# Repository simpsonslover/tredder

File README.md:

# DIY hardware wallet

A personal-project hardware crypto wallet: RP2350 (Pico 2 W) + NXP SE050C2 secure element, with a colour screen, 4 buttons, microSD encrypted backups, BLE to a phone app, and a LiPo battery.

**Security is the priority. When convenience and security conflict, security wins, and the trade-off is written down.**

| Phase | Status | Where |
|---|---|---|
| 1. PCB (KiCad) | rev A routed, ERC/DRC clean, 19/19 circuit simulations pass, BOM | [hardware/](hardware/README.md) |
| 2. Firmware (Pico C SDK) | M1 wallet core done (8 347 host checks pass); M2 secure storage + PIN next | [firmware/](firmware/README.md) |
| 3. Mobile app (Expo dev build) | all screens built; 127 tests, lint/tsc/expo-doctor clean, Android bundle builds; talks to the mock device until firmware M5 adds the secure channel | [app/](app/README.md) |
| 4. Enclosure (tamper-evident) | not started | `enclosure/` |

Device ↔ app protocol: [protocol/PROTOCOL.md](protocol/PROTOCOL.md).

**Dev stack:** `tools/devstack/devstack.ps1` starts an Android emulator with the app, plus the [tredder device simulator](sim/README.md), and connects them ([how](tools/devstack/README.md)).

Every chain is built against testnets first (Bitcoin testnet, Sepolia, Solana devnet).

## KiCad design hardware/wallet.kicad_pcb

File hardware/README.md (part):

# Phase 1: main board (rev A)

KiCad project: `wallet.kicad_pro`. The schematic is saved in KiCad 8 format and opens in KiCad 8, 9, and 10. The PCB file was written by KiCad 10.0.7, which is installed on this machine, so **open it with KiCad 10**. KiCad 8 can't open boards saved by newer versions.

Everything is generated from **[tools/design.py](tools/design.py)**, which defines parts, pins, nets, and part numbers. The schematic, PCB netlist, and BOM come from that one file, so they can't drift apart.

| File | What it is |
|---|---|
| `wallet.kicad_sch` | Schematic (label-style, one A2 sheet, grouped by function) |
| `wallet.kicad_pcb` | 4-layer, 85.6 × 54 mm (credit card) PCB |
| `wallet.kicad_sym`, `wallet.pretty/` | Project symbols and two custom footprints |
| `bom/wallet_bom_full.csv` | Full BOM: MPN, LCSC, notes, and a **VERIFY** column |
| `bom/wallet_bom_jlc.csv` | JLCPCB assembly BOM (parts JLC can place) |
| `erc.rpt`, `drc.rpt` | Last ERC/DRC results |
| `tools/build.ps1` | Regenerates everything and reruns ERC/DRC |
| `sim/` | Circuit simulation of the whole board (ngspice), 18 tests: see §9 and [sim/README.md](sim/README.md) |
| `wallet.kicad_dru` + `wallet.kicad_pro` constraints | **JLCPCB's published multilayer limits** (jlcpcb.com/capabilities/pcb-capabilities, read 2026-11-01; re-check before ordering): track/space 0.09, via 0.15/0.25, PTH ring ≥ 0.15, PTH hole to track ≥ 0.28, SMD pad spacing ≥ 0.15, pad to track ≥ 0.1, copper to edge ≥ 0.2, NPTH ≥ 0.5, inner hole clearances 0.2/0.3, silkscreen text ≥ 1.0 mm / line ≥ 0.15 mm. KiCad's DRC uses them automatically |
| `jlcpcb-4L-real.edru` | The same JLCPCB limits as a **Fusion** design-rules file (load it in Fusion's DRC). It cannot hold the PTH-to-PTH 0.45 mm, PTH-hole-to-track 0.28 mm, NPTH and silkscreen limits; those are checked on the KiCad side. Also inside `mech/tredder-revA-fusion-ecad.zip` |
| `tools/gerber_drc.py` → `fab/gerber_drc.md` | **Independent DRC/DFM of the files the fab receives**, like EAGLE/Fusion's DRC and JLCPCB's DFM: renders the Gerbers at 10 µm (pygerber), reads the drill files and the IPC-D-356 netlist, and checks connectivity (opens = Fusion's air wires, shorts, inner planes included), clearance, width, annular rings, hole spacing, hole-to-copper, board edge, mask webs, silkscreen. Uses none of KiCad's checks. Proven on injected faults (missing plane, short, hairline). `export_fab.py` refuses to build the order if it reports an error. Needs `pip install pygerber numpy scipy pillow` |
| `tools/check_jlc.py` | JLCPCB hole-to-hole spacing (PTH ≥ 0.45 mm, other ≥ 0.2 mm), which KiCad 10's DRC does not check in this project; `export_fab.py` refuses to build the order without it |
| `tools/clean_tracks.py` | Removes Freerouting's duplicate segments and dead-end spurs (Fusion's "Wire Stub" check) without changing a connection; `route.py` runs it after every import |
| `tools/sync_values.py` | Pushes value-only changes from `design.py` into the routed PCB without touching copper |
| `breadboard/` | **Breadboard prototype** with the same Pico pins as the PCB: wiring picture, parts, wire-by-wire table, what it can and can't test (`tools/gen_breadboard.py`) |
| `mech/` | STEP for Fusion / MCAD: `tredder-revA.step` (detailed, for the enclosure) and `tredder-revA-sim.step` (clean solids for simulation). Setup: [mech/FUSION_SIM.md](mech/FUSION_SIM.md). Rebuild: `tools/export_mech.py` (KiCad python) |
| `mech/tredder-revA-fusion-ecad.zip` | The KiCad project for **Fusion's electronics import** (schematic + board). KiCad 10 writes nets in a form Fusion can't read (every pad comes in with no net), so `tools/export_fusion_ecad.py` writes the board with KiCad 9 net syntax and checks every net survives. Import `wallet.kicad_pro` from this zip, not from this folder |
| `3d/` | The project's own STEP models (display module, LiPo, and parts missing from KiCad's library), from `tools/gen_step_models.py` |

---

## 1. Block diagram

```
 USB-C ──F1──U1(ESD)──R3/R4(0Ω, DNP=charge-only)──► Pico TP2/TP3 (USB D-/D+)
   │ VBUS
   ├────────► Pico VBUS ──(Schottky on module)──► VSYS ◄──Q1 (load-share PFET)◄── SW1-A ◄── BT1 LiPo (J2)
   └──► U3 MCP73831 charger ───────────────────────────────────────────────────────┘ VBAT
                                                    SW1-B: 3V3_EN → GND (hard off, even on USB)

 Pico 2 W (RP2350 + CYW43439 BLE)
   I2C0  GP8/GP9  ──────► U2 NXP SE050C2         (VCC switched by Q2 = its reset; pull-ups on the SE supply)
   SPI0  GP0-3    ──────► J3 microSD            (VDD switched by Q3, soft-start, DET on GP6)
   SPI1  GP26/27  ──────► J4 2.0" ST7789 module (CS GP21, DC GP22, RST GP20, BL via Q4 on GP19,
                          module VCC switched by Q5 on GP18: unpowered in sleep)
   GP12-15        ──────► Back / Confirm / Up / Down (10k pull-ups + RC debounce)
   GP28 (ADC2)    ◄────── VBAT divider (after power switch, no drain when off)
   GP5            ◄────── charger STAT (5V→3.3V divider)
   SWD pads D1-D3 ──────► reachable from the back through the plated holes under the Pico (no debug connector)
```

## 2. Pin map

| GPIO | Function | | GPIO | Function |
|---|---|---|---|---|
| GP0 | SD MISO (SPI0 RX) | | GP14 | BTN UP |
| GP1 | SD CS (SPI0 CSn) | | GP15 | BTN DOWN |
| GP2 | SD SCK | | GP16 | unused |
| GP3 | SD MOSI | | GP17 | unused |
| GP4 | unused | | GP18 | LCD power enable (active low, Q5) |
| GP5 | CHG_STAT | | GP19 | LCD backlight (active low) |
| GP6 | SD card detect | | GP20 | LCD RST |
| GP7 | SD power enable (active low) | | GP21 | LCD CS |
| GP8 | SE SDA (I2C0) | | GP22 | LCD DC |
| GP9 | SE SCL (I2C0) | | GP26 | LCD SCK (SPI1) |
| GP10 | unused | | GP27 | LCD MOSI (SPI1) |
| GP11 | SE power enable (active low) | | GP28 | VBAT sense (ADC2) |
| GP12 | BTN BACK | | GP23-25, 29 | used inside the module by the radio |
| GP13 | BTN CONFIRM | | | |

All five switch controls (Q2 SE, Q3 SD, Q4 backlight, Q5 display power, and SW1) default to **off** when the MCU is in reset or unprogrammed.

## 3. Secure element: NXP SE050C2 (chosen over the SE050A2)

**U2 = NXP SE050C2, `SE050C2HQ1/Z01SDZ`** (HX2QFN20 / SOT1969-1: 3 × 3 × 0.32 mm, 0.4 mm pitch, centre pad to GND). **You buy it from an NXP-authorised distributor (Mouser / Digi-Key / Farnell) and solder it yourself.** It's left out of the JLCPCB BOM and placement file. LCSC lists it as C2659345, but with almost no stock.

**Why C2 rather than A2.** Both are the same chip, pinout and package, with the same certification (CC EAL6+), bus encryption (SCP03) and 50 kB of secure storage. The suffix is the configuration NXP loads at the factory:

| | **SE050C2** | SE050A2 |
|---|---|---|
| Public-key crypto | Full set: ECC (NIST, Brainpool, Ed25519/X25519, **Koblitz incl. secp256k1**) and RSA up to 4096 bit | A subset: ECC only, no RSA (NXP: the A/B variants "come with a subset of keys") |
| secp256k1, the Bitcoin/Ethereum curve | Users report ECDSA secp256k1 signing works on the C2 dev kit | Not confirmed for A |
| Dev kit for the breadboard | OM-SE050ARD is the C2 configuration | — |

The C2 gives up nothing against the A2, and keeps the option of doing secp256k1 operations inside the SE (for example a device attestation key the app can verify).

**What changed from the OPTIGA Trust M, and what that trades off:**

- **Bus protection.** The OPTIGA's Shielded Connection is replaced by the SE050's **Platform SCP03** (AES-encrypted and MACed APDUs). **Trade-off:** NXP publishes the default SCP03 keys for its dev kits, so the link is effectively plaintext until provisioning rotates them to device-unique keys stored in RP2350 OTP. Firmware must refuse to store any secret before that rotation.
- **PIN-gated secret.** On the SE050 this is an AES authentication object with MaxAttempts = 10 guarding a binary object (firmware `app/se.h`). **Trade-off:** Trezor's open-source PIN code was written for the OPTIGA. For the SE050 the references are NXP's AN12413 (APDU spec) and AN12514 (security guidelines), and Nitrokey 3, an open-source security key built on the SE050. The "attempt counted before the result" property must be re-verified on this chip in M2.
- **Soldering.** **Trade-off:** the pitch is 0.4 mm instead of 0.5 mm, which is harder by hand. Use flux, a fine tip or solder paste, and hot air or a hot plate, then check every side under a magnifier for bridges.
- **No reset pin.** The SE050 is reset by switching its supply off with Q2 for ≥ 40 ms (GP10 is now unused). ENA is tied high (deep power-down not used), VIN = VCC, VOUT open, and the unused contactless (LA/LB) and ISO7816 RST inputs go to GND, all per datasheet Table 5.
- **I2C pull-ups** R13/R14 now go to the switched SE supply, not +3V3, so an unpowered SE is never fed through its I/O pins.
- **Lifecycle.** Distributors list the SE050C2 as NRND (not recommended for new designs), with NXP steering new designs to newer SE05x parts. It is still stocked; **buy 2–3 spares now.**

**Phase 2 key scheme (design target):**
`seed_key = KDF(PIN-stretched secret, SE-held secret released after PIN check, RP2350 OTP secret)`.
An attacker needs the PIN, **and** must defeat the SE counter, **and** must read the MCU's OTP. Stealing one chip isn't enough.

## 4. Security decisions in this board (and what each trades away)

| Decision | Security gain | Convenience lost |
|---|---|---|
| R3/R4 0 Ω links on USB D+/D- (DNP in production) | Charge-only USB removes the whole USB stack and BOOTSEL/PICOBOOT as attack surface | Firmware updates then come via a signed image on microSD instead of USB |
| SW1 pole B grounds `3V3_EN` | Hard off, even when USB is plugged in; nothing runs while it's "off" | Can't wake from USB; must flip the switch |
| SE power switched (Q2), default off | Lets firmware hard-reset the SE and keep it unpowered when locked | One more GPIO and some firmware sequencing |
| Display module power-gated (Q5), and sleep locks the wallet | Sleep current 14 mA → 2.6 mA (≈ 8 days on BT1 instead of 1.5). Waking always needs the PIN, so a device left asleep is locked | Waking takes a button press + PIN; the display re-initialises (~0.3 s) |
| SD on its own SPI bus, power-gated (Q3) | Untrusted removable media can't share a bus with the display, and is unpowered unless in a backup flow | Need to power-cycle the card in firmware |
| No test points on SE I2C | Makes passive probing slightly harder (Platform SCP03 is the real defence) | Harder to debug the SE link (use a scope on the IC pins) |
| No debug connector or test pads (removed to keep the board simple) | Less to cover in production; SWD disabled in OTP anyway | Debugging means soldering wires to the Pico's underside SWD pads through the holes; voltages are probed on the parts themselves |
| External pull-ups on buttons | Immune to RP2350 erratum E9 (input pull-down latch) whatever the chip stepping | 8 passives |
| All parts on top, display module above them | Single-sided assembly is cheaper | Display must be removed to reach the Pico (BOOTSEL, SWD) |

## 5. Honest physical-security assessment

**What this design resists**
- **Lost or stolen device, casual or opportunistic attacker:** strong. Without the PIN, the seed is ciphertext in external flash. The SE wipes its secret after 10 tries, and that counter lives in the SE, not in the MCU.
- **Reading the flash chip** (desoldering the W25Q on the Pico module): gets ciphertext only. This is exactly why the seed must never be in flash in plain form.
- **Firmware replacement:** secure boot rejects unsigned images, and anti-rollback rejects old ones.
- **SWD debugging:** disabled permanently in OTP.
- **Sniffing the MCU↔SE bus:** defeated by Platform SCP03, once provisioning has replaced NXP's published default keys.

**What it does not fully resist (be aware)**
- **Fault injection on the RP2350 (voltage/EM/laser glitching).** In Raspberry Pi's 2024–25 RP2350 hacking challenge, researchers broke the A2 stepping with glitching, and one team extracted OTP secrets. The A4 stepping fixed several of these, and the glitch detectors help, but a well-equipped lab attacker with your device for days is **not** stopped by the RP2350 alone. That's why the SE secret is part of the key derivation: glitching the MCU alone then shouldn't be enough.
- **The SE itself:** EAL6+ resists most lab attacks within its certified scope, but no chip is unbreakable. A nation-state lab attack is out of scope.
- **Evil maid / supply-chain implant:** an attacker who opens the case, adds a keylogger on the buttons or a tap on the display SPI, and returns the device could capture the PIN or the seed shown during setup. Mitigations: the tamper-evident case (Phase 4), checking the seal every time, and a firmware attestation check against the SE (Phase 2). The board itself can't detect this when it's off; there's no battery-backed tamper mesh.
- **Wireless:** the CYW43439 runs a closed-source Infineon firmware blob loaded by the RP2350. A remote bug there is a real (if unlikely) risk. The BLE design treats the phone and the radio as untrusted (everything authenticated, confirm on device), but an air-gapped design such as SeedSigner or Coldcard with QR/SD is strictly safer. **This is the single biggest trade-off of putting Bluetooth in the device.**
- **Cold-boot / RAM remanence while unlocked:** the firmware wipes secrets after use, but an attacker who glitches a running, unlocked device has more options than one who gets a locked device.
- **$5 wrench attack:** use the BIP39 passphrase (hidden wallet) feature in Phase 2.

## 6. Check these before ordering ⚠

1. **SE050 footprint:** `NXP_HX2QFN-20-1EP_3x3mm_P0.4mm_EP1.7x1.7mm` is KiCad's WQFN-20 3×3 P0.4 land pattern (0.2 × 0.825 mm pads, 1.7 × 1.7 mm centre pad). It matches the EasyEDA footprint LCSC publishes for C2659345, and the pinout is datasheet rev 3.7 Figure 4 / Table 5. NXP's site blocks automated downloads, so I couldn't read the SOT1969-1 package drawing itself. **Compare the pads with NXP's SOT1969-1 "reflow soldering footprint" before ordering.**
2. **Display module pinout and outline:** J4 assumes the common 2.0" 240×320 ST7789V module order **GND, VCC, SCL, SDA, RES, DC, CS, BLK** and a ~60 × 36 mm outline (F.Fab rectangle). Waveshare and others use different orders. Buy the module first, then edit `NETS` in `design.py` to match. The firmware drives the panel landscape (`MADCTL 0x60` in `firmware/app/src/gfx.c`), assuming the module's native top edge points away from J4. If the picture is upside down on your module, use `0xA0`.
3. **LiPo connector polarity:** pin 1 = BAT+. Many cheap packs are wired reversed for JST-PH. A reversed pack destroys the charger. Use a cell **with a protection circuit (PCM)**, ≤ 50 × 34 × 6 mm to sit behind the board, ≥ 500 mAh (charge current is set to 500 mA by R5 = 2 kΩ). The design uses **BT1 = 1S LiPo "503035" (5.0 × 30 × 35 mm, 500 mAh, PCM, JST-PH 2.0 lead)**: not a board part: it is drawn as an outline on B.Fab, and its STEP model rides on J2, the connector it plugs into (`tools/add_battery.py`). This keeps every board part matched to a schematic symbol, which Fusion's import requires, stuck behind the left half with 0.5 mm foam tape, clear of the J4 header pins and the antenna. It is not in the JLC BOM: buy it separately and **check the lead polarity before plugging in**.
4. **LCSC numbers:** all checked against their LCSC product pages on 2026-11-02 (MPN, maker, value and package match for C1779, C19666, C22809, C4190, C23179, C424093). Stock was not visible there: JLCPCB's BOM step shows it for every line. Check it before paying.
5. **Pico 2 W underside pads:** USB D+/D- (TP2/TP3) and SWD (D1–D3) are **under** the module. The custom footprint adds 0.8 mm plated holes there so you can feed solder from the back. Otherwise reflow the module (stencil and hot plate). Test continuity before powering.
6. **Pico 2 W stepping:** confirm the RP2350 is stepping **A4** or later (the chip marking or `chip_id` in the bootrom). A4 includes the security fixes from the hacking challenge.
7. **Don't plug in both USB ports.** The Pico's own micro-USB is still on the module, under the display. Its VBUS ties to the same net. The case should block it.
8. **Antenna area:** keep metal (battery, screws, display frame) away from the right-hand 10 mm of the board. The battery must sit behind the left part of the board only (Phase 4).
9. **DPDT switch pinout:** this assumes the C&K JS202011JCQN pins 2 and 5 are the commons. Confirm with the datasheet.
10. **microSD card-detect:** this assumes the DM3AT DET switch closes to DET_A (tied to GND) when a card is inserted. Confirm with the datasheet; firmware can invert it if not.
11. **Routing:** see section 7. Review every autorouted trace yourself; don't send an autorouted security device to fab unseen.

## 7. Layout status

- Placement, board outline, 4-layer stack, and GND/3V3 pours are done.
  - In1 is solid GND.
  - In2 is a +3V3 plane.
  - The outer layers are GND fills.
- The Pico antenna keepout is respected.
- **Routing: complete draft.** GND/+3V3 pads get generated stub+via fanout to the planes (`gen_pcb.py: fanout`). The remaining signals were autorouted with Freerouting 2.1 (`tools/route.py`) on F.Cu/B.Cu only.
- **DRC: 0 unconnected, 0 clearance/short errors, 0 schematic-parity issues. ERC: 0 errors, 0 warnings.**
- What's left in `drc.rpt`:
  - 2 × "items not allowed": paste openings inside the stock Pico footprint's own RF keepout. These are harmless and come from the library footprint.
  - 2 × "starved thermal": USB-C shell tabs have one thermal spoke on F.Cu. They're still connected through the other layers.
  - Silkscreen overlap warnings: cosmetic, and JLC clips silk off pads.
- ⚠ **`tools/build.ps1 -Fresh` regenerates placement and DISCARDS routing.** After the first route, make changes in KiCad (F8 = update from schematic) or re-run `route.py`.

**Recommended manual clean-up in KiCad (before ordering):**
1. Fatten the VBUS, VBAT, and VSYS paths (≥ 0.5 mm) and keep them short.
2. Route USB D+/D- as a pair (USB 1.1 full-speed is forgiving, but keep it tidy).
3. Make sure no trace runs under the antenna keepout.
4. Stitch GND vias around the board edge and the Pico.
5. Run DRC with zero errors, then generate Gerbers using JLC's KiCad guide.

## 8. Bring-up / test plan (do this before Phase 2)

Test in this order and stop at the first failure.

1. **Bare board:** check continuity GND↔+3V3, GND↔VBUS, and GND↔VBAT. None should be shorted.
2. **Power, without the Pico:** connect USB-C through a USB power meter. Check:
   - VBUS is ~5 V.
   - The charger LED is off with no battery.
   - Adding the battery makes the LED light, and VBAT climbs to 4.2 V then the LED goes off.
3. **Fit the Pico.** Check:
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
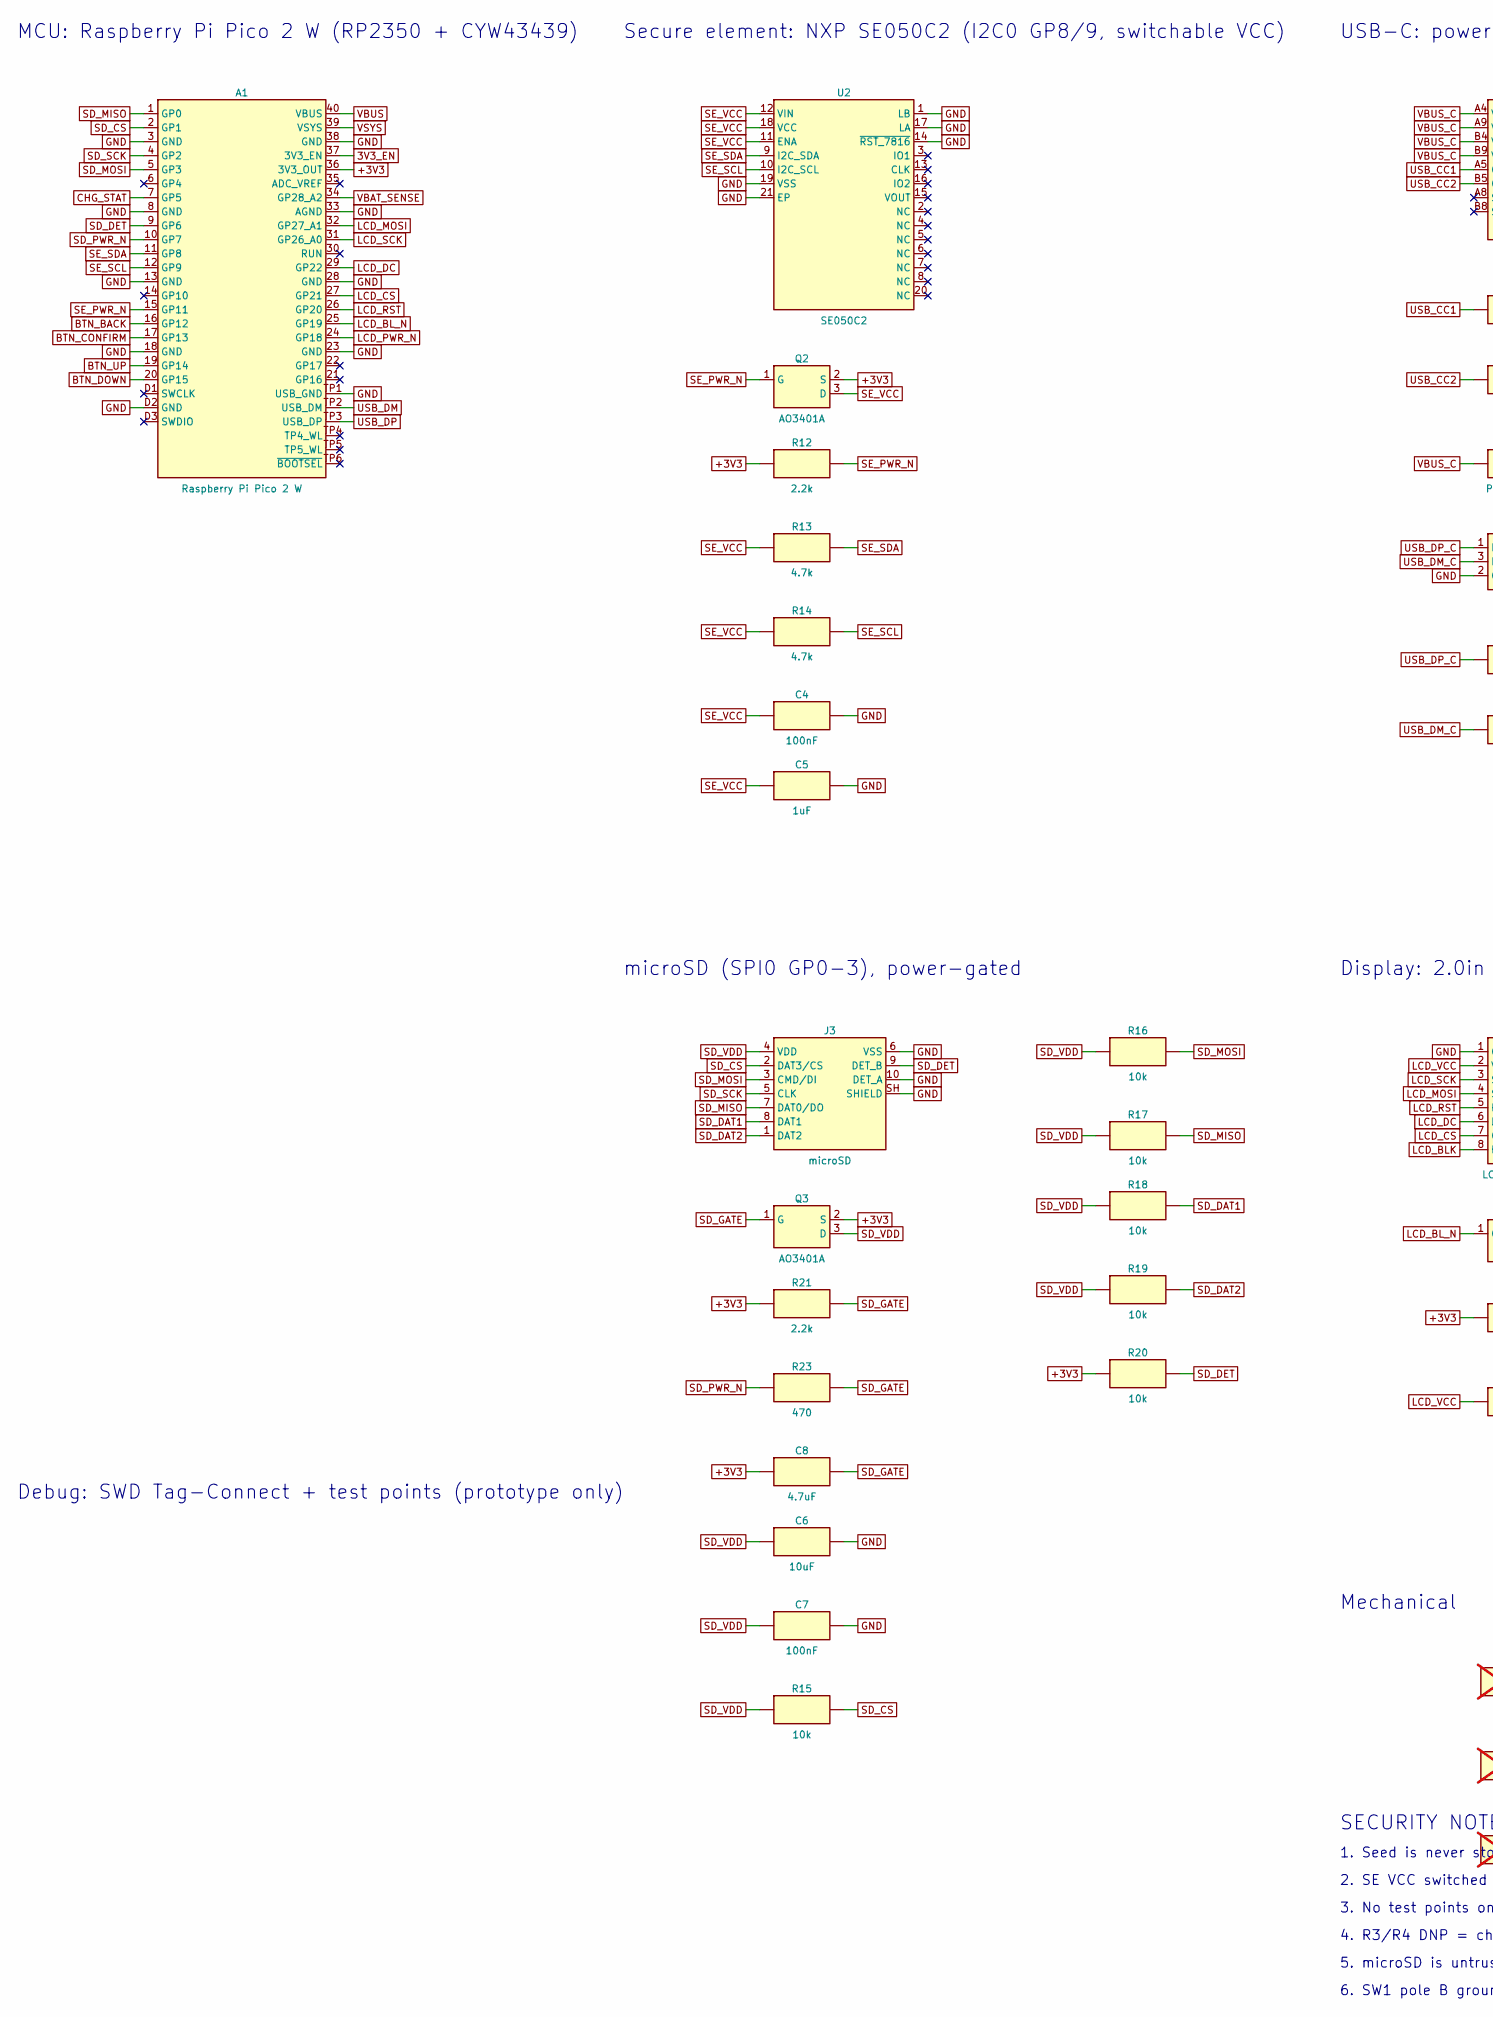
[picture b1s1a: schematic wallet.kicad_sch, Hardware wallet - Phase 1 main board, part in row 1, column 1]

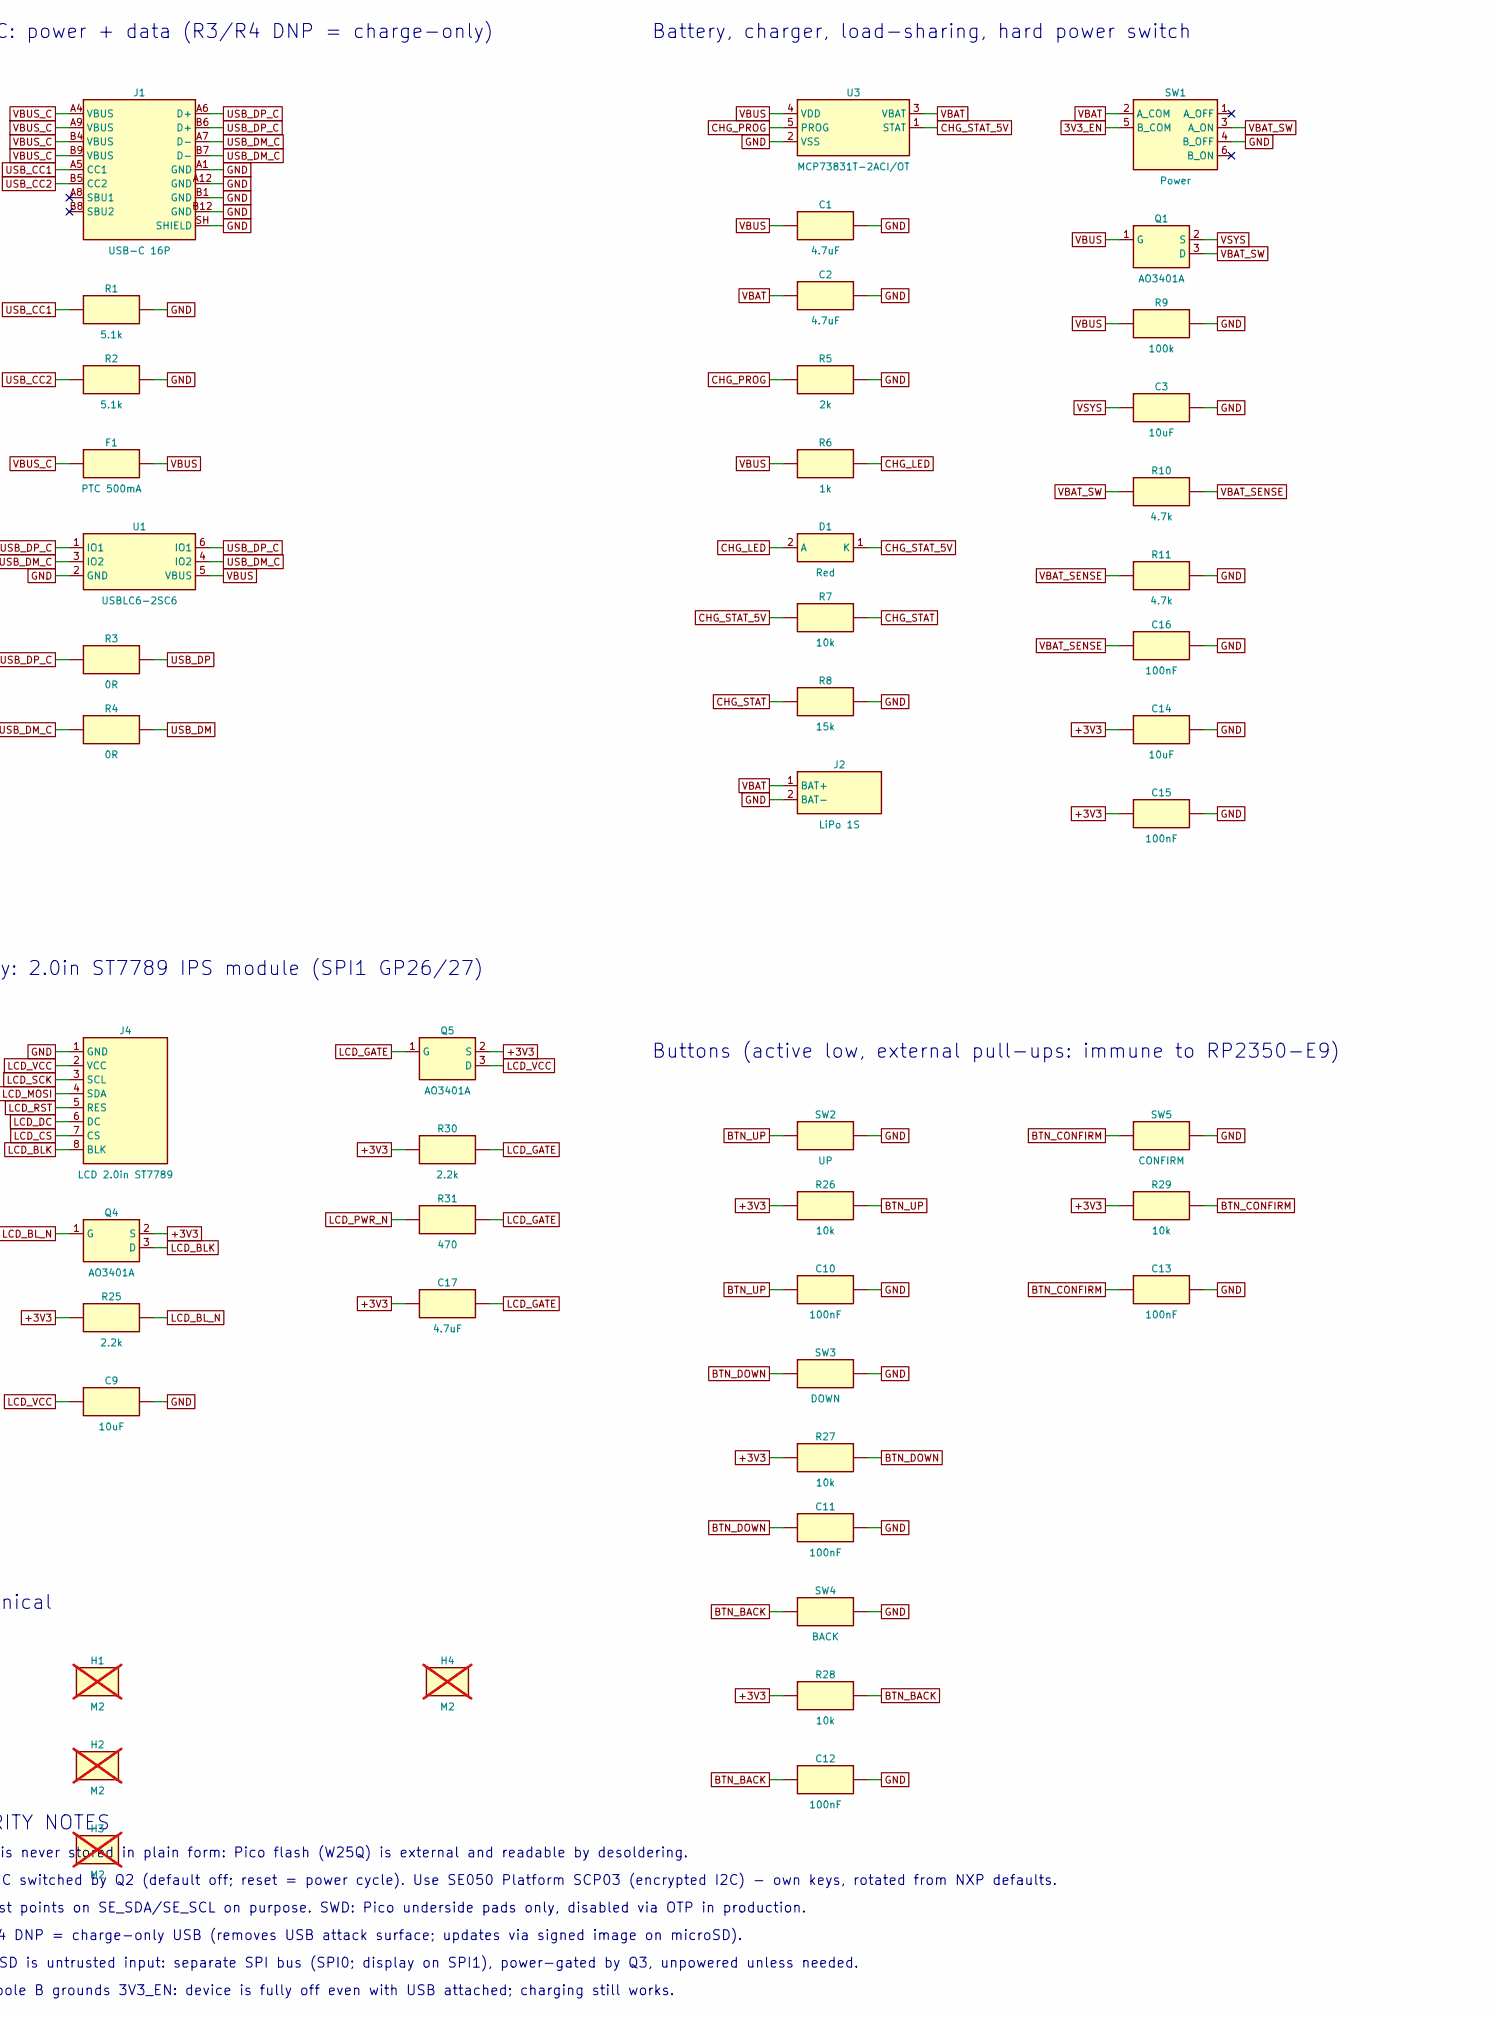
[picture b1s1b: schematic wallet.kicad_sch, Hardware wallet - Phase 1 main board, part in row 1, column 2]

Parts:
A1: Raspberry Pi Pico 2 W; RaspberryPi_Pico_2_W_SMD_SolderHoles; MPN SC1634 (Pico 2 W); LCSC C42394205
C1, C2: 4.7uF; C_0805_2012Metric; MPN CL21A475KAQNNNE; LCSC C1779
C3, C6, C9, C14: 10uF; C_0805_2012Metric; MPN CL21A106KAYNNNE; LCSC C15850
C4, C7, C10, C11, C12, C13, C15, C16: 100nF; C_0603_1608Metric; MPN CC0603KRX7R9BB104; LCSC C14663
C5: 1uF; C_0603_1608Metric; MPN CL10A105KB8NNNC; LCSC C15849
C8, C17: 4.7uF; C_0603_1608Metric; MPN CL10A475KO8NNNC; LCSC C19666
D1: Red; LED_0603_1608Metric; MPN KT-0603R; LCSC C2286
F1: PTC 500mA; Fuse_1206_3216Metric; MPN SMD1206-050 (JKSEMI, 6 V, 0.5 A hold, 1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; LCSC C2846128
H1, H2, H3, H4: M2; MountingHole_2.2mm_M2; MPN No part; not fitted
J1: USB-C 16P; USB_C_Receptacle_HRO_TYPE-C-31-M-12; MPN TYPE-C-31-M-12; LCSC C165948
J2: LiPo 1S; JST_PH_S2B-PH-SM4-TB_1x02-1MP_P2.00mm_Horizontal; MPN S2B-PH-SM4-TB(LF)(SN); LCSC C295747
J3: microSD; microSD_HC_Hirose_DM3AT-SF-PEJM5; MPN DM3AT-SF-PEJM5; LCSC C114218
J4: LCD 2.0in ST7789; PinSocket_1x08_P2.54mm_Vertical; MPN 2.54-1*8P female header, 8.5 mm (BOOMEL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; LCSC C27438
Q1, Q2, Q3, Q4, Q5: AO3401A; SOT-23; MPN AO3401A; LCSC C15127
R1, R2: 5.1k; R_0603_1608Metric; MPN 0603WAF5101T5E; LCSC C23186
R3, R4: 0R; R_0603_1608Metric; MPN 0603WAF0000T5E; LCSC C21189
R5: 2k; R_0603_1608Metric; MPN 0603WAF2001T5E; LCSC C22975
R6: 1k; R_0603_1608Metric; MPN 0603WAF1001T5E; LCSC C21190
R7, R15, R16, R17, R18, R19, R20, R26, R27, R28, R29: 10k; R_0603_1608Metric; MPN 0603WAF1002T5E; LCSC C25804
R8: 15k; R_0603_1608Metric; MPN 0603WAF1502T5E; LCSC C22809
R9: 100k; R_0603_1608Metric; MPN 0603WAF1003T5E; LCSC C25803
R10, R11, R13, R14: 4.7k; R_0603_1608Metric; MPN 0603WAF4701T5E; LCSC C23162
R12, R21, R25, R30: 2.2k; R_0603_1608Metric; MPN 0603WAF2201T5E; LCSC C4190
R23, R31: 470; R_0603_1608Metric; MPN 0603WAF4700T5E; LCSC C23179
SW1: Power; SW_DPDT_CK_JS202011JCQN; MPN JS202011JCQN; LCSC C221665
SW2: UP; SW_Push_1P1T_XKB_TS-1187A; MPN TS-1187A-B-A-B; LCSC C318884
SW3: DOWN; SW_Push_1P1T_XKB_TS-1187A; MPN TS-1187A-B-A-B; LCSC C318884
SW4: BACK; SW_Push_1P1T_XKB_TS-1187A; MPN TS-1187A-B-A-B; LCSC C318884
SW5: CONFIRM; SW_Push_1P1T_XKB_TS-1187A; MPN TS-1187A-B-A-B; LCSC C318884
U1: USBLC6-2SC6; SOT-23-6; MPN USBLC6-2SC6; LCSC C7519
U2: SE050C2; NXP_HX2QFN-20-1EP_3x3mm_P0.4mm_EP1.7x1.7mm; MPN SE050C2HQ1/Z01SDZ
U3: MCP73831T-2ACI/OT; SOT-23-5; MPN MCP73831T-2ACI/OT; LCSC C424093

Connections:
3V3_EN: A1.37 (3V3_EN), SW1.5 (B_COM)
+3V3: A1.36 (3V3_OUT), C8.1, C14.1, C15.1, C17.1, Q2.2 (S), Q3.2 (S), Q4.2 (S), Q5.2 (S), R12.1, R20.1, R21.1, R25.1, R26.1, R27.1, R28.1, R29.1, R30.1
BTN_BACK: A1.16 (GP12), C12.1, R28.2, SW4.1
BTN_CONFIRM: A1.17 (GP13), C13.1, R29.2, SW5.1
BTN_DOWN: A1.20 (GP15), C11.1, R27.2, SW3.1
BTN_UP: A1.19 (GP14), C10.1, R26.2, SW2.1
CHG_LED: D1.2 (A), R6.2
CHG_PROG: R5.1, U3.5 (PROG)
CHG_STAT: A1.7 (GP5), R7.2, R8.1
CHG_STAT_5V: D1.1 (K), R7.1, U3.1 (STAT)
GND: A1.3 (GND), A1.8 (GND), A1.13 (GND), A1.18 (GND), A1.23 (GND), A1.28 (GND), A1.33 (AGND), A1.38 (GND), A1.D2 (GND), A1.TP1 (USB_GND), C1.2, C2.2, C3.2, C4.2, C5.2, C6.2, C7.2, C9.2, C10.2, C11.2, C12.2, C13.2, C14.2, C15.2, C16.2, J1.A1 (GND), J1.A12 (GND), J1.B1 (GND), J1.B12 (GND), J1.SH (SHIELD), J2.2 (BAT-), J3.6 (VSS), J3.10 (DET_A), J3.SH (SHIELD), J4.1 (GND), R1.2, R2.2, R5.2, R8.2, R9.2, R11.2, SW1.4 (B_OFF), SW2.2, SW3.2, SW4.2, SW5.2, U1.2 (GND), U2.1 (LB), U2.14 (~RST_7816), U2.17 (LA), U2.19 (VSS), U2.21 (EP), U3.2 (VSS)
LCD_BLK: J4.8 (BLK), Q4.3 (D)
LCD_BL_N: A1.25 (GP19), Q4.1 (G), R25.2
LCD_CS: A1.27 (GP21), J4.7 (CS)
LCD_DC: A1.29 (GP22), J4.6 (DC)
LCD_GATE: C17.2, Q5.1 (G), R30.2, R31.2
LCD_MOSI: A1.32 (GP27_A1), J4.4 (SDA)
LCD_PWR_N: A1.24 (GP18), R31.1
LCD_RST: A1.26 (GP20), J4.5 (RES)
LCD_SCK: A1.31 (GP26_A0), J4.3 (SCL)
LCD_VCC: C9.1, J4.2 (VCC), Q5.3 (D)
SD_CS: A1.2 (GP1), J3.2 (DAT3/CS), R15.2
SD_DAT1: J3.8 (DAT1), R18.2
SD_DAT2: J3.1 (DAT2), R19.2
SD_DET: A1.9 (GP6), J3.9 (DET_B), R20.2
SD_GATE: C8.2, Q3.1 (G), R21.2, R23.2
SD_MISO: A1.1 (GP0), J3.7 (DAT0/DO), R17.2
SD_MOSI: A1.5 (GP3), J3.3 (CMD/DI), R16.2
SD_PWR_N: A1.10 (GP7), R23.1
SD_SCK: A1.4 (GP2), J3.5 (CLK)
SD_VDD: C6.1, C7.1, J3.4 (VDD), Q3.3 (D), R15.1, R16.1, R17.1, R18.1, R19.1
SE_PWR_N: A1.15 (GP11), Q2.1 (G), R12.2
SE_SCL: A1.12 (GP9), R14.2, U2.10 (I2C_SCL)
SE_SDA: A1.11 (GP8), R13.2, U2.9 (I2C_SDA)
SE_VCC: C4.1, C5.1, Q2.3 (D), R13.1, R14.1, U2.11 (ENA), U2.12 (VIN), U2.18 (VCC)
USB_CC1: J1.A5 (CC1), R1.1
USB_CC2: J1.B5 (CC2), R2.1
USB_DM: A1.TP2 (USB_DM), R4.2
USB_DM_C: J1.A7 (D-), J1.B7 (D-), R4.1, U1.3 (IO2), U1.4 (IO2)
USB_DP: A1.TP3 (USB_DP), R3.2
USB_DP_C: J1.A6 (D+), J1.B6 (D+), R3.1, U1.1 (IO1), U1.6 (IO1)
VBAT: C2.1, J2.1 (BAT+), SW1.2 (A_COM), U3.3 (VBAT)
VBAT_SENSE: A1.34 (GP28_A2), C16.1, R10.2, R11.1
VBAT_SW: Q1.3 (D), R10.1, SW1.3 (A_ON)
VBUS: A1.40 (VBUS), C1.1, F1.2, Q1.1 (G), R6.1, R9.1, U1.5 (VBUS), U3.4 (VDD)
VBUS_C: F1.1, J1.A4 (VBUS), J1.A9 (VBUS), J1.B4 (VBUS), J1.B9 (VBUS)
VSYS: A1.39 (VSYS), C3.1, Q1.2 (S)

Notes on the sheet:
MCU: Raspberry Pi Pico 2 W (RP2350 + CYW43439)
Secure element: NXP SE050C2 (I2C0 GP8/9, switchable VCC)
USB-C: power + data (R3/R4 DNP = charge-only)
Battery, charger, load-sharing, hard power switch
microSD (SPI0 GP0-3), power-gated
Display: 2.0in ST7789 IPS module (SPI1 GP26/27)
Buttons (active low, external pull-ups: immune to RP2350-E9)
Debug: SWD Tag-Connect + test points (prototype only)
Mechanical
SECURITY NOTES
1. Seed is never stored in plain form: Pico flash (W25Q) is external and readable by desoldering.
2. SE VCC switched by Q2 (default off; reset = power cycle). Use SE050 Platform SCP03 (encrypted I2C) - own keys, rotated from NXP defaults.
3. No test points on SE_SDA/SE_SCL on purpose. SWD: Pico underside pads only, disabled via OTP in production.
4. R3/R4 DNP = charge-only USB (removes USB attack surface; updates via signed image on microSD).
5. microSD is untrusted input: separate SPI bus (SPI0; display on SPI1), power-gated by Q3, unpowered unless needed.
6. SW1 pole B grounds 3V3_EN: device is fully off even with USB attached; charging still works.

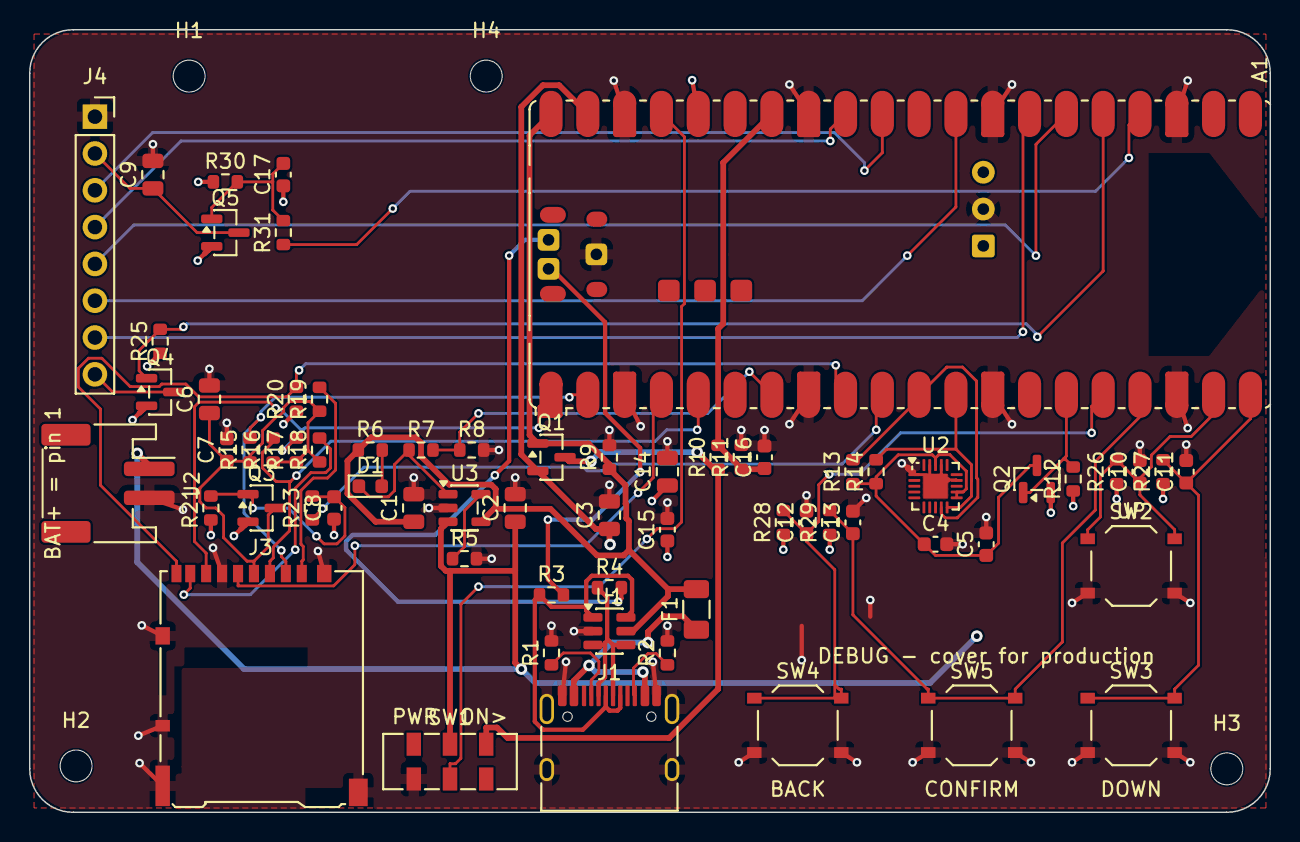
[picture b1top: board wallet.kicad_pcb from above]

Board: 4 copper layers, 85.6 x 54.0 mm, 70 parts (0 on the bottom side), 47 nets.

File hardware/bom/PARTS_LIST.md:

# Parts list: one tredder (rev A)

Generated by `hardware/tools/gen_bom.py` from `design.py` (do not edit by hand). Machine-readable versions: `wallet_bom_full.csv`, `wallet_bom_jlc.csv`.

**VERIFY** = the LCSC number, stock or pinout was not confirmed: look it up before ordering (hardware/README.md section 6).

## Summary

| What | Where | Line items | Parts |
|---|---|---|---|
| PCB, 4-layer | JLCPCB (or any fab) | 1 | 1 |
| Parts JLCPCB sources (LCSC) and assembles | JLCPCB assembly | 30 | 65 |
| Parts you buy and solder (not on the JLCPCB order) | Mouser / Digi-Key | 1 | 1 |
| Off-board parts | various | 6 | 9 |
| Not fitted (pads, holes) | - | 1 | 0 |

66 components on the board: JLCPCB assembles all of them **except U2, the NXP SE050C2 secure element, which you buy and solder** (section 3). The display module and the battery plug in.

## 1. Circuit board

| Item | Spec |
|---|---|
| Size | 85.6 x 54.0 mm (credit card), 3 mm corner radius |
| Layers | 4: F.Cu signals / In1 GND / In2 +3V3 / B.Cu signals + GND |
| Thickness | 1.6 mm FR-4 |
| Finish | ENIG preferred (flat pads for the castellated Pico 2 W and the 0.4 mm-pitch SE050) |
| Files | `wallet.kicad_pcb`: export Gerbers + drill from KiCad |
| Assembly | JLCPCB **Standard PCBA**, top side only: SMT + one through-hole part (J4) |

## 2. JLCPCB sources and assembles (`wallet_bom_jlc.csv`)

| Qty | Designators | Value | Part number | LCSC | Package |
|---|---|---|---|---|---|
| 1 | A1 | Raspberry Pi Pico 2 W | SC1634 (Pico 2 W) | C42394205 | RaspberryPi_Pico_2_W_SMD_SolderHoles |
| 2 | C1 C2 | 4.7uF | CL21A475KAQNNNE | C1779 | C_0805_2012Metric |
| 4 | C3 C6 C9 C14 | 10uF | CL21A106KAYNNNE | C15850 | C_0805_2012Metric |
| 8 | C4 C7 C10 C11 C12 C13 C15 C16 | 100nF | CC0603KRX7R9BB104 | C14663 | C_0603_1608Metric |
| 1 | C5 | 1uF | CL10A105KB8NNNC | C15849 | C_0603_1608Metric |
| 2 | C8 C17 | 4.7uF | CL10A475KO8NNNC | C19666 | C_0603_1608Metric |
| 1 | D1 | Red | KT-0603R | C2286 | LED_0603_1608Metric |
| 1 | F1 | PTC 500mA | SMD1206-050 (JKSEMI, 6 V, 0.5 A hold, 1 A trip) | C2846128 | Fuse_1206_3216Metric |
| 1 | J1 | USB-C 16P | TYPE-C-31-M-12 | C165948 | USB_C_Receptacle_HRO_TYPE-C-31-M-12 |
| 1 | J2 | LiPo 1S | S2B-PH-SM4-TB(LF)(SN) | C295747 | JST_PH_S2B-PH-SM4-TB_1x02-1MP_P2.00mm_Horizontal |
| 1 | J3 | microSD | DM3AT-SF-PEJM5 | C114218 | microSD_HC_Hirose_DM3AT-SF-PEJM5 |
| 1 | J4 | LCD 2.0in ST7789 | 2.54-1*8P female header, 8.5 mm (BOOMELE) | C27438 | PinSocket_1x08_P2.54mm_Vertical |
| 5 | Q1 Q2 Q3 Q4 Q5 | AO3401A | AO3401A | C15127 | SOT-23 |
| 2 | R1 R2 | 5.1k | 0603WAF5101T5E | C23186 | R_0603_1608Metric |
| 2 | R3 R4 | 0R | 0603WAF0000T5E | C21189 | R_0603_1608Metric |
| 1 | R5 | 2k | 0603WAF2001T5E | C22975 | R_0603_1608Metric |
| 1 | R6 | 1k | 0603WAF1001T5E | C21190 | R_0603_1608Metric |
| 11 | R7 R15 R16 R17 R18 R19 R20 R26 R27 R28 R29 | 10k | 0603WAF1002T5E | C25804 | R_0603_1608Metric |
| 1 | R8 | 15k | 0603WAF1502T5E | C22809 | R_0603_1608Metric |
| 1 | R9 | 100k | 0603WAF1003T5E | C25803 | R_0603_1608Metric |
| 4 | R10 R11 R13 R14 | 4.7k | 0603WAF4701T5E | C23162 | R_0603_1608Metric |
| 4 | R12 R21 R25 R30 | 2.2k | 0603WAF2201T5E | C4190 | R_0603_1608Metric |
| 2 | R23 R31 | 470 | 0603WAF4700T5E | C23179 | R_0603_1608Metric |
| 1 | SW1 | Power | JS202011JCQN | C221665 | SW_DPDT_CK_JS202011JCQN |
| 1 | SW2 | UP | TS-1187A-B-A-B | C318884 | SW_Push_1P1T_XKB_TS-1187A |
| 1 | SW3 | DOWN | TS-1187A-B-A-B | C318884 | SW_Push_1P1T_XKB_TS-1187A |
| 1 | SW4 | BACK | TS-1187A-B-A-B | C318884 | SW_Push_1P1T_XKB_TS-1187A |
| 1 | SW5 | CONFIRM | TS-1187A-B-A-B | C318884 | SW_Push_1P1T_XKB_TS-1187A |
| 1 | U1 | USBLC6-2SC6 | USBLC6-2SC6 | C7519 | SOT-23-6 |
| 1 | U3 | MCP73831T-2ACI/OT | MCP73831T-2ACI/OT | C424093 | SOT-23-5 |

## 3. You buy and solder (not on the JLCPCB order)

| Qty | Designators | Part | Part number | LCSC | Notes |
|---|---|---|---|---|---|
| 1 | U2 | SE050C2 | SE050C2HQ1/Z01SDZ | - | You buy and solder this one: Mouser / Digi-Key / Farnell (NXP authorised). The C2 variant: ECC incl. secp256k1 + RSA, CC EAL6+. LCSC lists it as C2659345 with little stock. |

## 4. Off the board

| Item | Qty | Spec | Where | Notes |
|---|---|---|---|---|
| Display module (screen) | 1 | 2.0" IPS TFT 240x320, ST7789V/V2, SPI, 3.3 V, 8-pin 2.54 mm header in the order GND VCC SCL SDA RES DC CS BLK: **ZJY200S10Z0TG01** (sold as "2.0 inch IPS TFT 240x320 ST7789", e.g. tinytronics.nl, AliExpress) | AliExpress / TinyTronics (not stocked at LCSC) | Plugs into J4. Check the pin order printed on its back before ordering boards (README section 6.2); outline about 60 x 36 mm. NOT the Waveshare 2inch module: its pins are in a different order on a PH2.0 connector. |
| Battery (BT1) | 1 | 1S LiPo 503035, 3.7 V 500 mAh, 5.0 x 30 x 35 mm, WITH protection PCM, JST-PH 2.0 mm 2-pin lead | battery shop / AliExpress | Behind the left half of the board (tools/add_battery.py). CHECK the lead polarity: pin 1 = BAT+. 500 mAh matches the 500 mA charge current (1 C). |
| Foam tape | 1 | double-sided foam tape, 0.5 mm, about 30 x 25 mm | any | Holds the cell to the back of the board. |
| Screws | 4 | M2 low-head (wafer / pan) screws, length to suit the case | any | H1-H4. H1 and H4 sit under the display module: low head only. |
| microSD card | 1 | microSD, small capacity (1-8 GB), industrial / high-endurance grade | any reputable brand | For the encrypted backup. Treat it as untrusted media; it is only powered during a backup. |
| USB-C cable | 1 | USB-C, data-capable for the prototype | any | Charging and (prototype only) firmware loading. Production can be charge-only (R3/R4 not fitted). |

## 5. Not fitted (footprints only)

| Designators | What |
|---|---|
| H1 H2 H3 H4 | M2: No part |

## 6. Optional: development tools and Phase 4

| Item | Qty | Spec | Where | Notes |
|---|---|---|---|---|
| Debug probe | 1 | Raspberry Pi Debug Probe (or any CMSIS-DAP probe) | Raspberry Pi resellers | Optional: SWD debugging via the Pico's underside pads D1-D3 (wires soldered through the holes from the back). Firmware loads over USB-C without it. |
| Enclosure | 1 | tamper-evident case (Phase 4, not designed yet) | 3D print | Leaves room for the 5.5 mm cell behind the board. |

## Before you order

1. Buy the display module first and check its pin order and outline against J4.
2. Check every **VERIFY** LCSC number and its stock.
3. Check the battery lead polarity (pin 1 = BAT+) before plugging it in: a reversed pack destroys the charger.
4. Order the NXP SE050C2 (U2) from Mouser, Digi-Key or Farnell: SE050C2HQ1/Z01SDZ (buy 2-3: it is NRND). Buying it yourself from an NXP-authorised distributor also means you know where the chip your PIN protection depends on came from. Fitting it: 3 x 3 mm, 0.4 mm pitch, with a centre pad to GND: flux, solder paste and hot air or a hot plate, then check every side for bridges.
5. Check JLCPCB's assembly preview (part rotations) before paying.

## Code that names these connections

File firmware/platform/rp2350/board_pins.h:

/* GENERATED by firmware/tools/gen_board_pins.py from hardware/tools/design.py. Do not edit. */
#ifndef BOARD_PINS_H
#define BOARD_PINS_H

#define PIN_SD_MISO      0u  /* SPI0 RX [SD_MISO] */
#define PIN_SD_CS        1u  /* SPI0 CSn (driven as GPIO) [SD_CS] */
#define PIN_SD_SCK       2u  /* SPI0 SCK [SD_SCK] */
#define PIN_SD_MOSI      3u  /* SPI0 TX [SD_MOSI] */
#define PIN_CHG_STAT     5u  /* input, no pull: low = charging, high = done / no USB [CHG_STAT] */
#define PIN_SD_DET       6u  /* card detect, low = inserted (verify DM3AT switch polarity) [SD_DET] */
#define PIN_SD_PWR_N     7u  /* low = SD card powered (Q3) [SD_PWR_N] */
#define PIN_SE_SDA       8u  /* I2C0 SDA (4.7k pull-up to the switched SE supply; no internal pulls) [SE_SDA] */
#define PIN_SE_SCL       9u  /* I2C0 SCL (4.7k pull-up to the switched SE supply; no internal pulls) [SE_SCL] */
#define PIN_SE_PWR_N    11u  /* low = SE050 powered (Q2); the SE050 has no reset pin: reset = power cycle [SE_PWR_N] */
#define PIN_BTN_BACK    12u  /* active low, external pull-up + RC debounce [BTN_BACK] */
#define PIN_BTN_CONFIRM 13u  /* active low, external pull-up + RC debounce [BTN_CONFIRM] */
#define PIN_BTN_UP      14u  /* active low, external pull-up + RC debounce [BTN_UP] */
#define PIN_BTN_DOWN    15u  /* active low, external pull-up + RC debounce [BTN_DOWN] */
#define PIN_LCD_PWR_N   18u  /* low = display module powered (Q5); drive LCD pins LOW before power-off [LCD_PWR_N] */
#define PIN_LCD_BL_N    19u  /* low = backlight on (Q4), PWM capable [LCD_BL_N] */
#define PIN_LCD_RST     20u  /* ST7789 reset, active low [LCD_RST] */
#define PIN_LCD_CS      21u  /* ST7789 CS (GPIO) [LCD_CS] */
#define PIN_LCD_DC      22u  /* ST7789 data/command [LCD_DC] */
#define PIN_LCD_SCK     26u  /* SPI1 SCK [LCD_SCK] */
#define PIN_LCD_MOSI    27u  /* SPI1 TX [LCD_MOSI] */
#define PIN_VBAT_ADC    28u  /* ADC2; VBAT = 2 x reading (calibrate per device) [VBAT_SENSE] */

#define BOARD_SD_SPI   spi0
#define BOARD_LCD_SPI  spi1
#define BOARD_SE_I2C   i2c0
#define BOARD_VBAT_ADC_INPUT 2u
#define BOARD_VBAT_DIVIDER_NUM 94u
#define BOARD_VBAT_DIVIDER_DEN 47u
/* charger STAT divider bottom resistor: R8 = 15k */

#endif

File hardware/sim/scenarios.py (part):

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        res.between(f"[VBAT {vb} V] 3V3 steady state", float(v3[-1]), 3.2, 3.4)
        res.le(f"[VBAT {vb} V] 3V3 overshoot", float(v3.max()), 3.6)
        res.info(f"[VBAT {vb} V] battery current, idle (MCU 60 mA)", float(r["i(vbat)"][-1]) * 1e3, "mA")
        res.le(f"[VBAT {vb} V] SE_VCC glitch during power-up (GPIOs in reset)", float(V(r, "SE_VCC").max()), 0.3)
        res.le(f"[VBAT {vb} V] SD_VDD glitch during power-up (GPIOs in reset)", float(V(r, "SD_VDD").max()), 0.3)
        res.le(f"[VBAT {vb} V] backlight current during power-up", float(r["i(vj4blm)"].max()) * 1e3, 1.0, "mA")
        invariants(res, r, None)
        if vb == 3.7:
            save_plot(res, r, [dict(ylabel="V", series=[("VBAT", V(r, "VBAT")), ("VSYS", V(r, "VSYS")),
                                                       ("3V3", v3), ("3V3_EN", V(r, "3V3_EN"))])],
                      xscale=1e3, xlabel="time (ms)")
    return res
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        res.le(f"[PTC {fr} Ohm] peak VBUS on board (abs max)", float(V(r, "VBUS").max()), VBUS_ABS)
        invariants(res, r, c)
        if fr == 0.15:
            save_plot(res, r, [dict(ylabel="V", series=[("VBUS_C (connector)", V(r, "VBUS_C")), ("VBUS (after F1)", V(r, "VBUS")),
                                                       ("VSYS", V(r, "VSYS"))], limits=[("6.0 V", VBUS_ABS), ("5.5 V", 5.5)])],
                      title="USB hot-plug ringing, PTC 0.15 Ohm", xscale=1e3, xlabel="time (ms)")
    c = cfg(battery=dict(v=3.7), usb=dict(v=5.0, L=1e-6, R=0.1, plug=[(0, 0), (2e-3, 0), (2.001e-3, 1),
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    res.info("Time Q1 body diode carries the load after unplug (VSYS < VBAT - 0.3 V)",
             float(np.ptp(t[diode])) * 1e3 if diode.any() else 0.0, "ms")
    invariants(res, r, c)
    save_plot(res, r, [dict(ylabel="V", series=[("VBUS", vbus), ("VSYS", vsys), ("VBAT", V(r, "VBAT")), ("3V3", v3)]),
                       dict(ylabel="A", series=[("battery charge (+) / discharge (-)", ibat)])],
              title="USB plug at 2 ms, unplug at 40 ms", xscale=1e3, xlabel="time (ms)")
    return res
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    toff = cross(t, lv, 0.3, rising=False, after=30e-3)
    res.info("LCD_VCC below 0.3 V after power-off", (toff - 30e-3) * 1e3 if toff else 999, "ms", kind="RULE")
    invariants(res, r, c)
    save_plot(res, r, [dict(ylabel="V", series=[("LCD_VCC", lv), ("3V3", v3), ("LCD_GATE", V(r, "LCD_GATE"))])],
              xscale=1e3, xlabel="time (ms)")
    r2 = sim(cfg(gpio={"GP18": ("pwl", on), "GP21": ("pwl", [(0, 0), (5e-3, 3.3)]), "GP22": ("pwl", [(0, 0), (5e-3, 3.3)]),
                       "GP20": "low", "GP26": "low", "GP27": "low", "GP19": "high"},
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    tdone = cross(t, stat, RP_VIH)
    res.info("Time to 'complete' (2 mAh scaled cell)", tdone or -1, "s")
    invariants(res, r, c)
    save_plot(res, r, [dict(ylabel="V", series=[("VBAT", vb), ("CHG_STAT (GP5)", stat)], limits=[("4.2 V", 4.2)]),
                       dict(ylabel="A", series=[("charge current", ib)])])
    return res

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    res.info("SD_VDD fall below 0.5 V after power-off (card reset needs < 0.5 V for >= 1 ms)",
             (t_off - 30e-3) * 1e3 if t_off else 999, "ms", kind="RULE")
    invariants(res, r, c)
    save_plot(res, r, [dict(ylabel="V", series=[("SD_VDD", sd), ("3V3", v3), ("SD_GATE", V(r, "SD_GATE"))]),
                       dict(ylabel="A", series=[("3V3 regulator output", ireg)])], xscale=1e3, xlabel="time (ms)")
    c2 = cfg(gpio={"GP7": ("pwl", on), "GP1": ("pwl", [(0, 0), (2.5e-3, 3.3)]), "GP2": "low", "GP3": "low",
                   "GP0": "z"}, **dict(base, analysis=".tran 5u 100m 0 50u"))
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    toff = cross(t, se, 0.3, rising=False, after=21e-3)
    res.info("SE_VCC below 0.3 V after power-off (hibernate)", (toff - 21e-3) * 1e3 if toff else 999, "ms", kind="RULE")
    invariants(res, r, c)
    save_plot(res, r, [dict(ylabel="V", series=[("SE_VCC", se), ("SE_SDA", V(r, "SE_SDA")),
                                               ("SE_PWR_N (GP11)", V(r, "SE_PWR_N"))])], xscale=1e3, xlabel="time (ms)")
    res.le("SE_SDA idle level with the SE off (pull-ups follow the SE supply)",
           float(V(r, "SE_SDA")[-1]), 0.3)
    r2 = sim(cfg(battery=dict(v=3.7), gpio={"GP11": ("pwl", on), "GP8": "high"}, analysis=".tran 2u 300m 0 50u"))
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    res.le("SDA rise time 30->70 % (Fast-mode 400 kHz)", tr, 300, "ns")
    res.le("SDA rise time 30->70 % (Fast-mode Plus 1 MHz)", tr, 120, "ns", kind="WARN")
    res.le("SDA low level (VOL)", float(window(r, sda, 2.5e-6, 3.2e-6).min()), 0.4)
    save_plot(res, r, [dict(ylabel="V", series=[("SE_SDA", sda)], limits=[("70 %", 0.7 * vdd), ("30 %", 0.3 * vdd)])],
              xscale=1e6, xlabel="time (us)")
    return res

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    res.le("Press detected after first contact", ((tpress or 1) - 1e-3) * 1e6, 100, "us")
    res.le("Release detected after last bounce", ((trel or 1) - 20.36e-3) * 1e3, 5, "ms")
    res.le("Pressed level", float(window(r, v, 2e-3, 19e-3).max()), RP_VIL)
    save_plot(res, r, [dict(ylabel="V", series=[("BTN_CONFIRM (GP13)", v)], limits=[("VIH 2.0", RP_VIH), ("VIL 0.8", RP_VIL)]),
                       dict(ylabel="contact", series=[("switch closed", r["v(btn_sw5)"])])], xscale=1e3, xlabel="time (ms)")
    return res

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    res.le("Backlight turn-on time 10-90 %", ((trise - tstart) if trise and tstart else 1) * 1e6, 20, "us")
    invariants(res, r, c)
    save_plot(res, r, [dict(ylabel="mA", series=[("backlight", ibl * 1e3)]),
                       dict(ylabel="V", series=[("LCD_BL_N (GP19)", V(r, "LCD_BL_N"))])], xscale=1e3, xlabel="time (ms)")
    return res


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    res.le("Peak 3V3 output current", float(i3.max()) * 1e3, 300, "mA", kind="WARN")
    res.info("Peak battery current", float(r["i(vbat)"].max()), "A")
    invariants(res, r, c)
    save_plot(res, r, [dict(ylabel="V", series=[("3V3", v3), ("VSYS", vsys)]),
                       dict(ylabel="A", series=[("3V3 load", i3), ("battery", r["i(vbat)"])])], xscale=1e3, xlabel="time (ms)")
    return res

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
